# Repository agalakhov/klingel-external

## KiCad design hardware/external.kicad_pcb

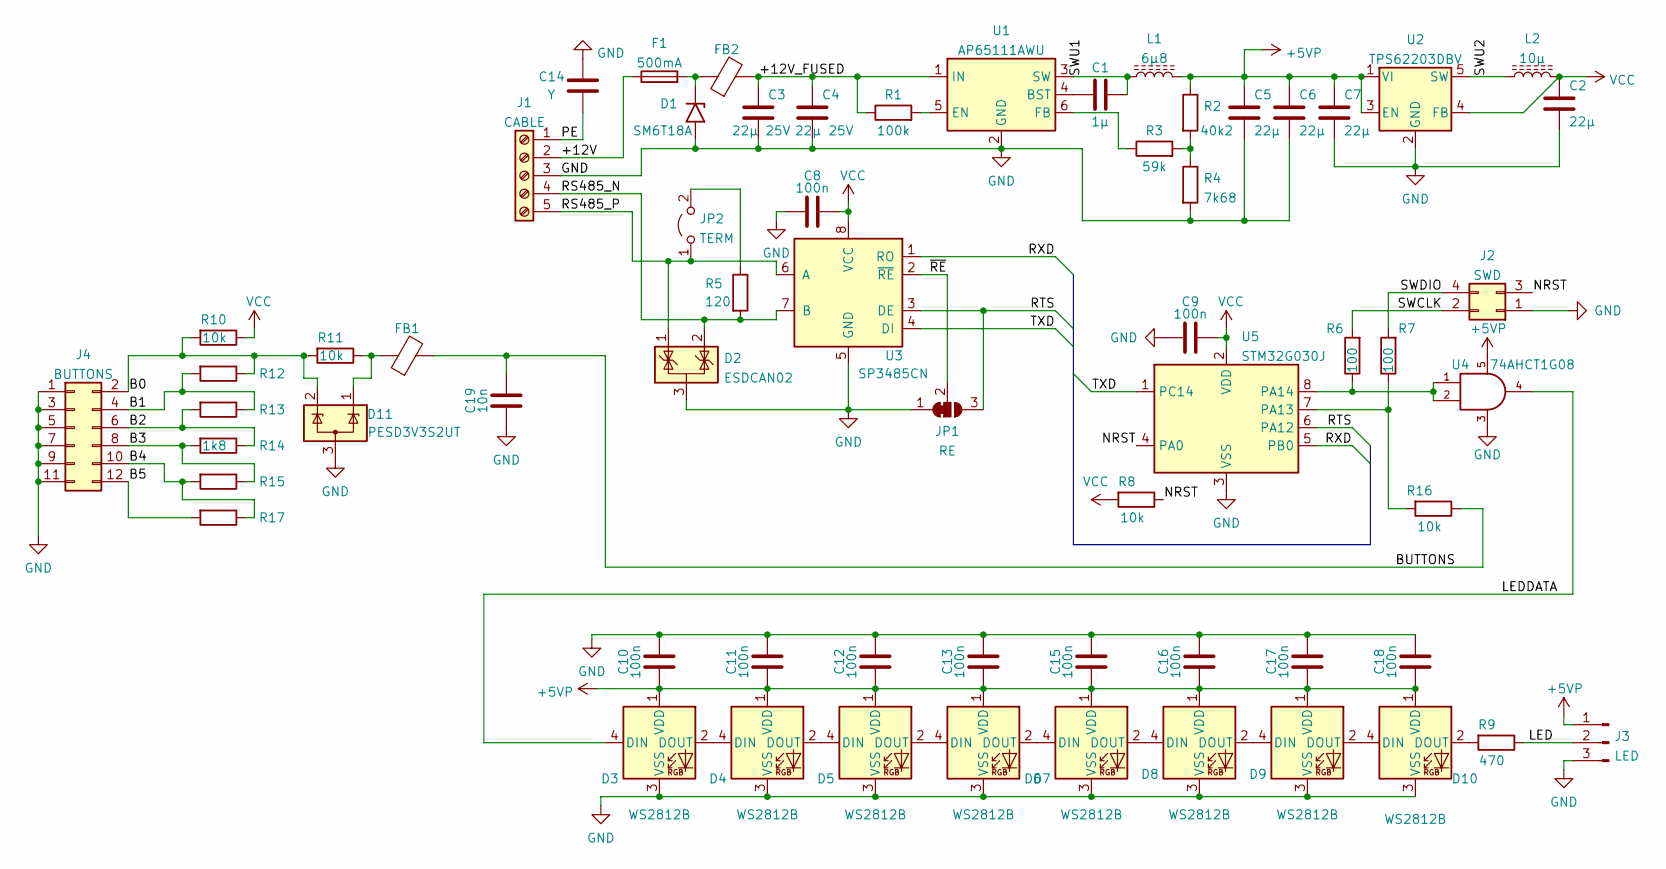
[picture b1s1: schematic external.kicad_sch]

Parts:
C1: 1µ; C_0805_2012Metric
C2, C5, C6, C7: 22µ; C_0805_2012Metric
C3, C4: 22µ 25V; C_0805_2012Metric
C8, C9, C10, C11, C12, C13, C15, C16, C17, C18: 100n; C_0805_2012Metric
C14: Y; C_1812_4532Metric
C19: 10n; C_0805_2012Metric
D1: SM6T18A; D_SMB
D2: ESDCAN02; SOT-23
D3, D4, D5, D6, D7, D8, D9, D10: WS2812B; LED_WS2812B_PLCC4_5.0x5.0mm_P3.2mm
D11: PESD3V3S2UT; SOT-23
F1: 500mA; Fuse_0805_2012Metric_Pad1.15x1.40mm_HandSolder
FB1, FB2: FerriteBead; L_0805_2012Metric
J1: CABLE; TerminalBlock_Phoenix_MPT-0,5-5-2.54_1x05_P2.54mm_Horizontal
J2: SWD; PinHeader_2x02_P2.54mm_Vertical
J3: LED; PinHeader_1x03_P2.54mm_Vertical
J4: BUTTONS; PinHeader_2x06_P2.54mm_Vertical
JP1: RE; SolderJumper-3_P1.3mm_Open_RoundedPad1.0x1.5mm
JP2: TERM; PinHeader_1x02_P2.54mm_Vertical
L1: 6µ8; L_Taiyo-Yuden_NR-50xx
L2: 10µ; L_Coilcraft_XxL4030
R1: 100k; R_0805_2012Metric
R2: 40k2; R_0805_2012Metric
R3: 59k; R_0805_2012Metric
R4: 7k68; R_0805_2012Metric
R5: 120; R_0805_2012Metric
R6, R7: 100; R_0805_2012Metric
R8, R10, R11, R16: 10k; R_0805_2012Metric
R9: 470; R_0805_2012Metric
R12, R13, R15, R17: R_0805_2012Metric
R14: 1k8; R_0805_2012Metric
U1: AP65111AWU; TSOT-23-6
U2: TPS62203DBV; SOT-23-5
U3: SP3485CN; SOIC-8_3.9x4.9mm_P1.27mm
U4: 74AHCT1G08; SOT-353_SC-70-5
U5: STM32G030J; SOIC-8_3.9x4.9mm_P1.27mm

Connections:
+5VP: C5.1, C6.1, C7.1, C10.1, C11.1, C12.1, C13.1, C15.1, C16.1, C17.1, C18.1, D3.1 (VDD), D4.1 (VDD), D5.1 (VDD), D6.1 (VDD), D7.1 (VDD), D8.1 (VDD), D9.1 (VDD), D10.1 (VDD), J3.1, L1.2, R2.1, U2.1 (VI), U2.3 (EN), U4.5 (VCC)
/+12V: F1.1, J1.2
/+12V_FUSED: C3.1, C4.1, FB2.2, R1.1, U1.1 (IN)
/B0: D11.2 (K), J4.2, R10.2, R11.2, R12.1
/B1: J4.4, R12.2, R13.1
/B2: J4.6, R13.2, R14.1
/B3: J4.8, R14.2, R15.1
/B4: J4.10, R15.2, R17.1
/B5: J4.12, R17.2
/BUTTONS: C19.2, FB1.2, R16.1
/LED: J3.2, R9.1
/LEDDATA: D3.4 (DIN), U4.4
/NRST: J2.3, R8.1, U5.4 (PA0)
/PE: C14.2, J1.1
/RS485_N: D2.2 (K), J1.4, R5.2, U3.7 (B)
/RS485_P: D2.1 (K), J1.5, JP2.1 (A), U3.6 (A)
/RTS: JP1.3 (B), U3.3 (DE), U5.6 (PA12)
/RXD: U3.1 (RO), U5.5 (PB0)
/SWCLK: J2.2, R6.2
/SWDIO: J2.4, R7.2
/SWU1: C1.2, L1.1, U1.3 (SW)
/SWU2: L2.1, U2.5 (SW)
/TXD: U3.4 (DI), U5.1 (PC14)
/~RE: JP1.2 (C), U3.2 (~RE)
GND: C2.2, C3.2, C4.2, C5.2, C6.2, C7.2, C8.1, C9.1, C10.2, C11.2, C12.2, C13.2, C14.1, C15.2, C16.2, C17.2, C18.2, C19.1, D1.2 (A2), D2.3 (A), D3.3 (VSS), D4.3 (VSS), D5.3 (VSS), D6.3 (VSS), D7.3 (VSS), D8.3 (VSS), D9.3 (VSS), D10.3 (VSS), D11.3 (A), J1.3, J2.1, J3.3, J4.1, J4.3, J4.5, J4.7, J4.9, J4.11, JP1.1 (A), R4.2, U1.2 (GND), U2.2 (GND), U3.5 (GND), U4.3 (GND), U5.3 (VSS)
unnamed: C1.1, U1.4 (BST)
unnamed: D1.1 (A1), F1.2, FB2.1
unnamed: D3.2 (DOUT), D4.4 (DIN)
unnamed: D4.2 (DOUT), D5.4 (DIN)
unnamed: D5.2 (DOUT), D6.4 (DIN)
unnamed: D6.2 (DOUT), D7.4 (DIN)
unnamed: D7.2 (DOUT), D8.4 (DIN)
unnamed: D8.2 (DOUT), D9.4 (DIN)
unnamed: D10.2 (DOUT), R9.2
unnamed: D9.2 (DOUT), D10.4 (DIN)
unnamed: D11.1 (K), FB1.1, R11.1
unnamed: JP2.2 (B), R5.1
unnamed: R1.2, U1.5 (EN)
unnamed: R2.2, R3.2, R4.1
unnamed: R3.1, U1.6 (FB)
unnamed: R6.1, U4.1, U4.2, U5.8 (PA14)
unnamed: R7.1, R16.2, U5.7 (PA13)
VCC: C2.1, C8.2, C9.2, L2.2, R8.2, R10.1, U2.4 (FB), U3.8 (VCC), U5.2 (VDD)

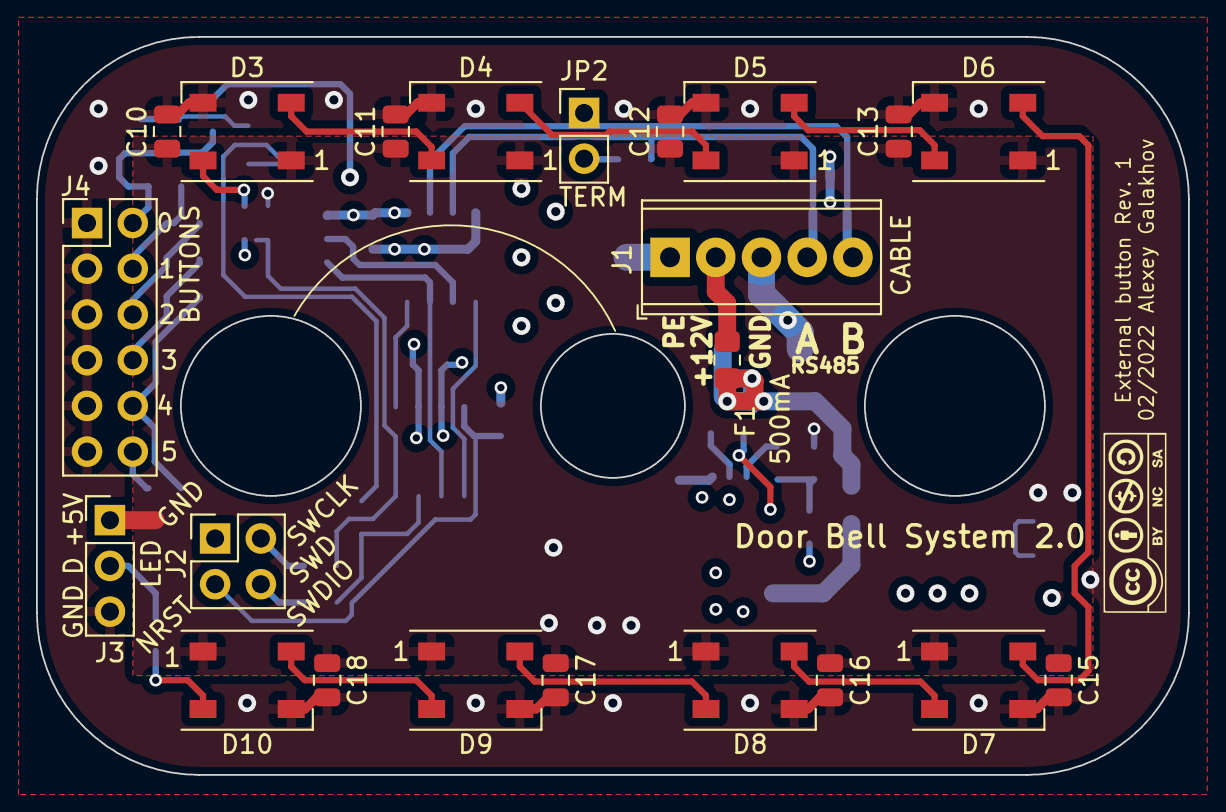
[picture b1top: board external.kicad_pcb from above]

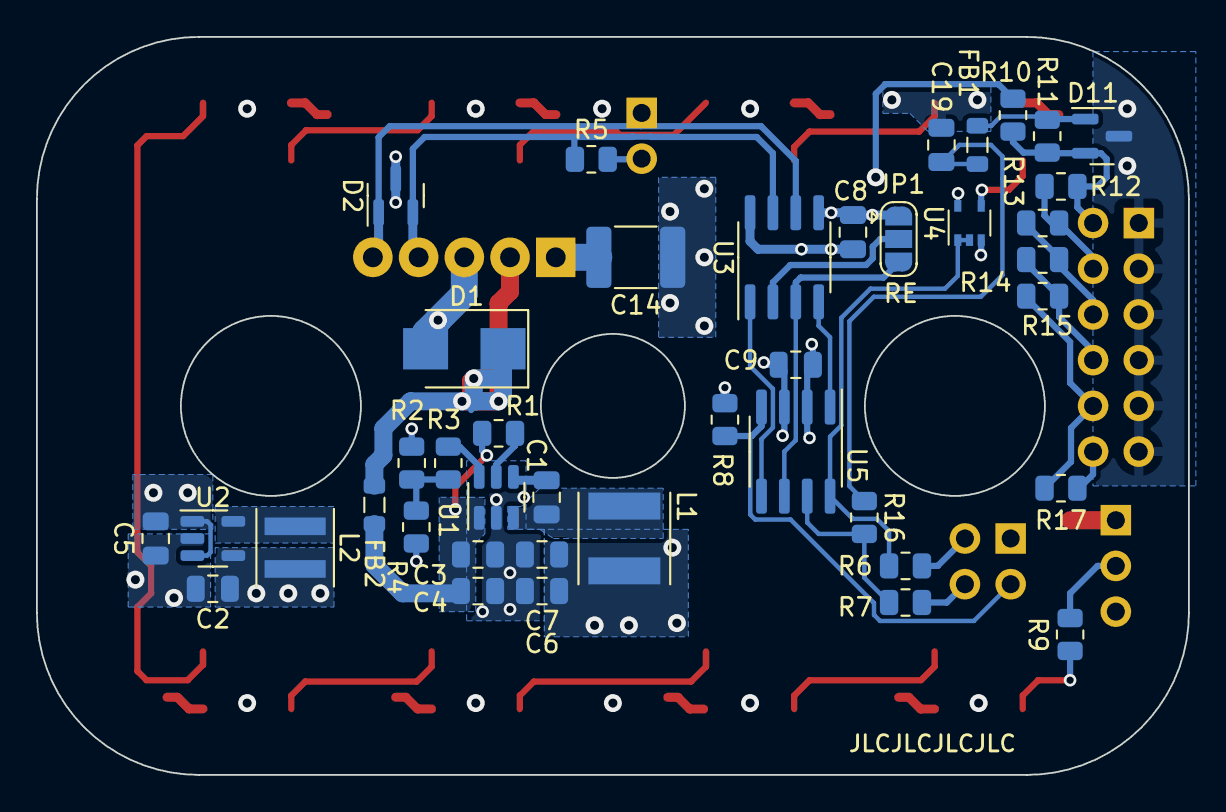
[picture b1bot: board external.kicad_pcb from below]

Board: 4 copper layers, 64.0 x 41.0 mm, 63 parts (41 on the bottom side), 43 nets.

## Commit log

2022-05-01 WIP before RTIC
2022-09-30 WIP, mostly working
2022-10-01 Working version, DMA not guarded, no CRC check
2022-10-01 Bus busy handling
2022-10-04 refactor: unite RS485 RX and TX
2022-10-04 refactor: rewrite transmit code
2022-10-04 Correct protocol handling
2022-10-15 led: support intensity scaling and glowing
2022-10-15 led: correct blinking periods
2022-10-15 led: add one-time effects
2022-10-15 led: support effects
2022-10-15 led: rework dirty state
2022-10-15 led: correct effects
2022-10-15 chore: reformat
2022-10-16 uptime: support uptime counter with TIM16
2022-10-16 rs485: support alone detection
2023-10-21 rs485: fix intensity handling
2023-10-21 chore: update dependencies
2023-11-04 rs485: swap A and B pins
2023-11-05 chore: update HAL to 0.2.0
2023-11-05 watchdog: reduce timeout to 3 secs
2023-11-06 rs485: handle bus collisions
2023-11-07 rs485: stop processing at error detection
2023-11-09 rs485: increase buffer size
2024-01-23 Add hardware project
